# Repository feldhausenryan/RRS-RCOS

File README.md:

# RRS-RCOS
Open Source Schematics, Code, etc.

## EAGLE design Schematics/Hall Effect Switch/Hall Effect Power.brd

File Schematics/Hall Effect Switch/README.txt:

The hall effect switch is a magnetic on/off switch.

Applying a magnet will turn the switch ON or OFF, causing the input Vin+ and Gnd to be applied to Vout+ and Gnd.
Reversing the magnetic field will reverse the state of the switch.

STATUS: 
Hall Effect Power.brd - Broken

TODO: Add parts list

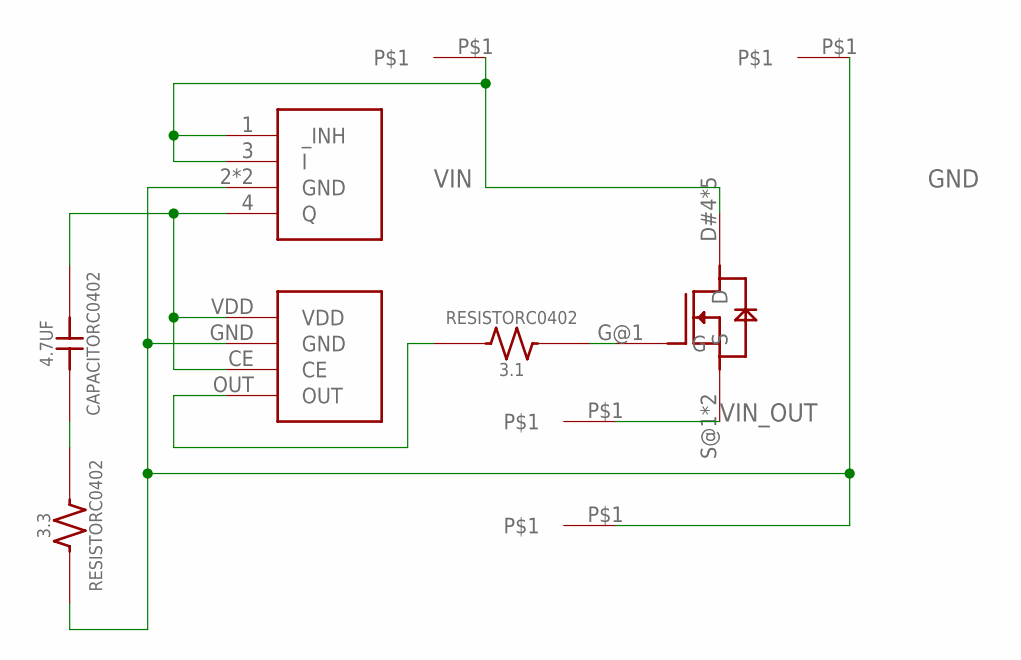
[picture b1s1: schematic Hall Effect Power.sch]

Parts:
3.1: RESISTORC0402; C0402; DIGIKEY# 1276-4368-1-ND
3.3: RESISTORC0402; C0402; DIGIKEY# 311-3.3JRCT-ND
4.7UF: CAPACITORC0402; C0402; DIGIKEY# 1276-6819-1-ND
U$1: HALL-MOSFET-NEW; DIGIKEY# SIAA40DJ-T1-GE3CT-ND
U$2: HALL-HALL-NEW; DIGIKEY# 1662-1657-1-ND
U$3: HALL-REG-NEW; DIGIKEY# IFX20001MBV33HTSA1CT-ND
U$4, U$5, U$6, U$7: SINGLE-WIRE

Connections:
GND: 3.3.1, U$2.GND, U$3.2 (GND), U$3.5 (GND), U$4.P$1, U$7.P$1
HALL_OUT: 3.1.2, U$2.OUT
unnamed: 4.7UF.2 (B), U$2.CE, U$2.VDD, U$3.4 (Q)
unnamed: 3.3.2, 4.7UF.1 (A)
unnamed: 3.1.1, U$1.G@1 (G)
VIN: U$1.D#4 (D), U$1.D@1 (D), U$1.D@2 (D), U$1.D@3 (D), U$1.D@5 (D), U$3.1 (_INH), U$3.3 (I), U$6.P$1
VIN_OUT: U$1.S@1 (S), U$1.S@2 (S), U$5.P$1

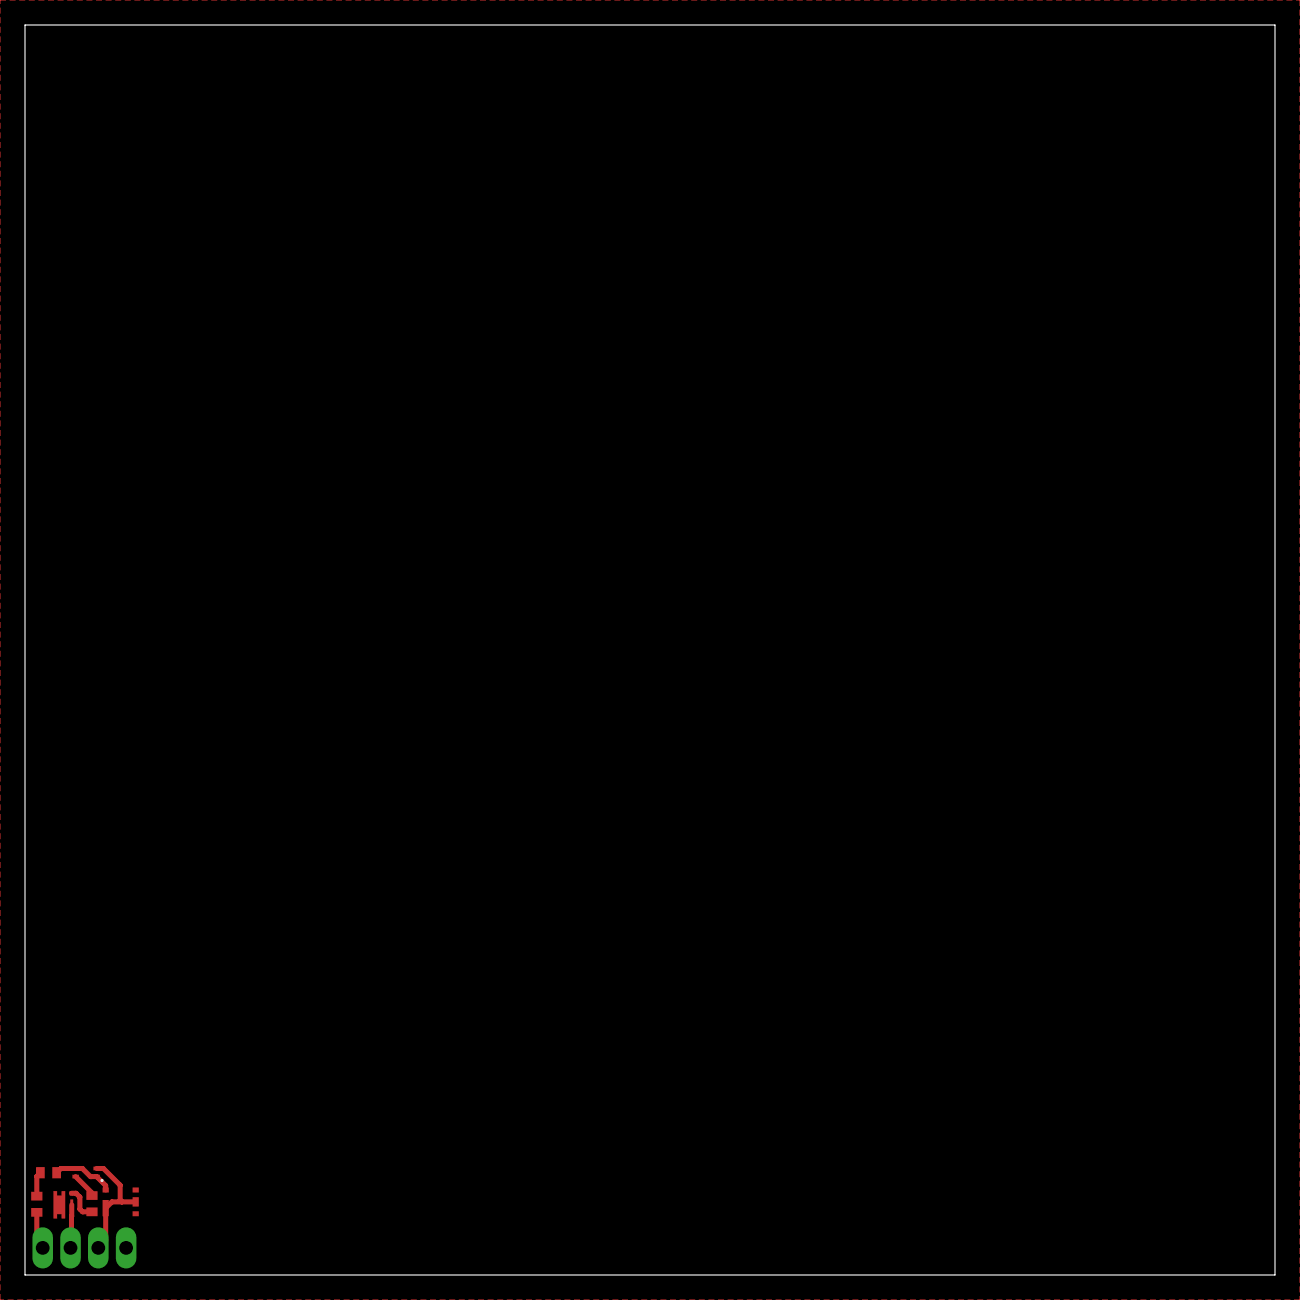
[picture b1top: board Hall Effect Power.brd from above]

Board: 2 copper layers, 100.0 x 100.0 mm, 10 parts (0 on the bottom side), 7 nets.

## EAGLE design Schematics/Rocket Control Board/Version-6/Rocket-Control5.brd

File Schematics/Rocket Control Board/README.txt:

October 18, 2016 by Ryan Feldhausen

The Rocket Control Board is an Arduino Zero clone. 
In the future the board will be used to mount various surface mounted components to 
create an Arduino compatible rocket control board.

Folder Contents
Misc - Various pictures or other files that may aid the development or understanding
       of the schematics or boards in this section.
	   
Version - The various stages of development of the schematic / board for this section. 
          There is no guarantee that any of the Version-X folders will contain 
		  functional schematics or boards.

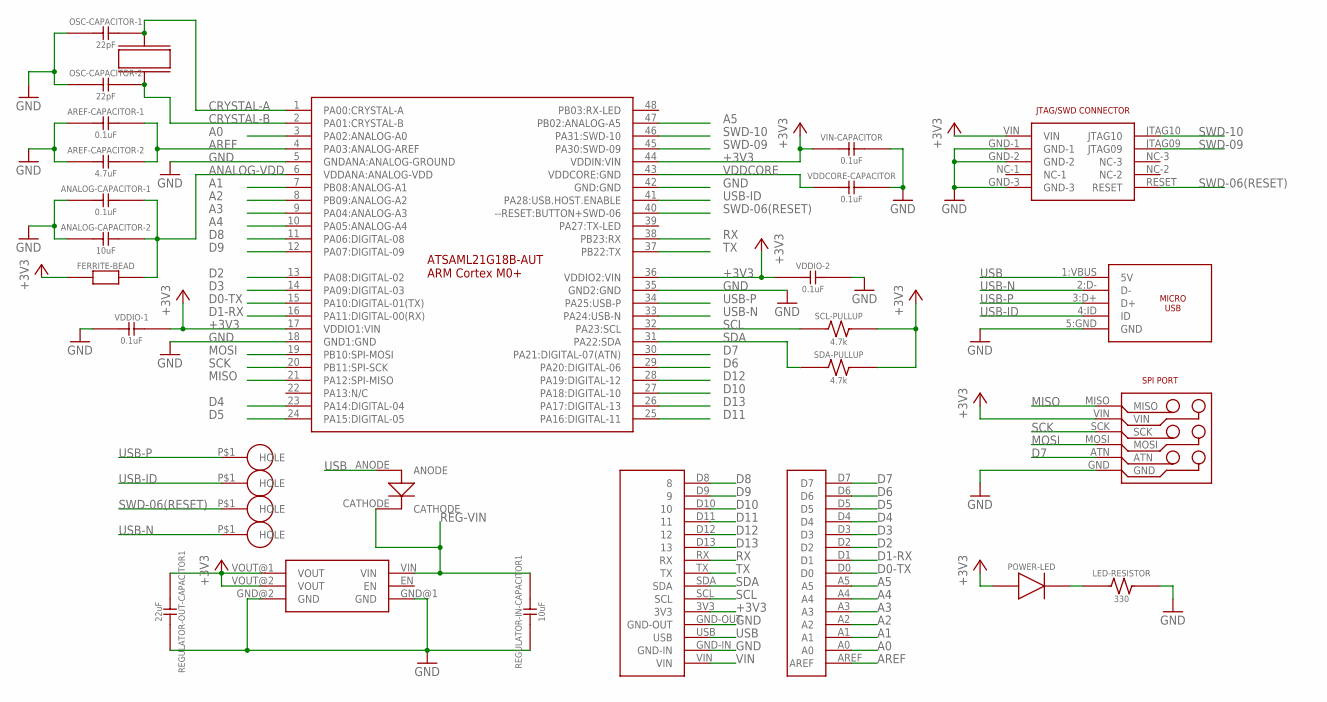
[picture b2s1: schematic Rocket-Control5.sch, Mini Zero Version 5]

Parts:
ANALOG-CAPACITOR-1: 0.1uF; C0402; DIGIKEY# 1276-1022-1-ND
ANALOG-CAPACITOR-2: 10uF; C0402; DIGIKEY# 1276-1450-1-ND
AREF-CAPACITOR-1: 0.1uF; C0402; DIGIKEY# 1276-1022-1-ND
AREF-CAPACITOR-2: 4.7uF; C0402; DIGIKEY# 1276-1173-1-ND
ARM-CORTEX-MO+: ATSAML21G18B-AUT; TQFP48; DIGIKEY# 1611-ATSAML21G18B-AUTCT-ND
FERRITE-BEAD: BLM18PG471SN1D; C0603; DIGIKEY# 490-5223-1-ND
HEADER-SIDE-A: HEADER-SIDE-A
HEADER-SIDE-B: HEADER-SIDE-B; DIGIKEY# S1011EC-40-ND
JTAG-CONNECTOR: JTAG-MINI; DIGIKEY# 609-3712-ND
LED-RESISTOR: 330; C0603; DIGIKEY# 1276-5050-1-ND
MICRO-USB-CONNECTOR: 10118194-0001LF; DIGIKEY# 609-4618-1-ND
OSC-CAPACITOR-1, OSC-CAPACITOR-2: 22pF; C0603; DIGIKEY# 1276-2229-1-ND
POWER-LED: APTD1608ZGC; C0603; DIGIKEY# 754-1547-1-ND
REGULATOR-IN-CAPACITOR1: 10uF; C0402; DIGIKEY# 1276-1450-1-ND
REGULATOR-OUT-CAPACITOR1: 22uF; C0402; DIGIKEY# 1276-6834-1-ND
SCL-PULLUP: 4.7k; C0402; DIGIKEY# 1276-5078-1-ND
SDA-PULLUP: 4.7k; C0402; DIGIKEY# 1276-5078-1-ND
SPI-PORT: SPI-PORT
U$1: ABS07-32.768KHZ-T
U$2: MIC5528
U$3: DIODE-STANDARD
U$4, U$5, U$6, U$7: HEADER-HOLE
VDDCORE-CAPACITOR: 0.1uF; C0402; DIGIKEY# 1276-1022-1-ND
VDDIO-1, VDDIO-2: 0.1uF; C0402; DIGIKEY# 1276-1022-1-ND
VIN-CAPACITOR: 0.1uF; C0402; DIGIKEY# 1276-1022-1-ND

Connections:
+3V3: ARM-CORTEX-MO+.17 (VDDIO1:VIN), ARM-CORTEX-MO+.36 (VDDIO2:VIN), ARM-CORTEX-MO+.44 (VDDIN:VIN), FERRITE-BEAD.1, HEADER-SIDE-B.3V3, JTAG-CONNECTOR.VIN, POWER-LED.1, REGULATOR-OUT-CAPACITOR1.1 (A), SCL-PULLUP.2, SDA-PULLUP.2, SPI-PORT.VIN, U$2.VOUT@1 (VOUT), U$2.VOUT@2 (VOUT), VDDIO-1.2 (B), VDDIO-2.2 (B), VIN-CAPACITOR.1 (A)
A0: ARM-CORTEX-MO+.3 (PA02:ANALOG-A0), HEADER-SIDE-A.A0
A1: ARM-CORTEX-MO+.7 (PB08:ANALOG-A1), HEADER-SIDE-A.A1
A2: ARM-CORTEX-MO+.8 (PB09:ANALOG-A2), HEADER-SIDE-A.A2
A3: ARM-CORTEX-MO+.9 (PA04:ANALOG-A3), HEADER-SIDE-A.A3
A4: ARM-CORTEX-MO+.10 (PA05:ANALOG-A4), HEADER-SIDE-A.A4
A5: ARM-CORTEX-MO+.47 (PB02:ANALOG-A5), HEADER-SIDE-A.A5
ANALOG-VDD: ANALOG-CAPACITOR-1.2 (B), ANALOG-CAPACITOR-2.2 (B), ARM-CORTEX-MO+.6 (VDDANA:ANALOG-VDD), FERRITE-BEAD.2
AREF: AREF-CAPACITOR-1.2 (B), AREF-CAPACITOR-2.2 (B), ARM-CORTEX-MO+.4 (PA03:ANALOG-AREF), HEADER-SIDE-A.AREF
CRYSTAL-A: ARM-CORTEX-MO+.1 (PA00:CRYSTAL-A), OSC-CAPACITOR-1.2 (B), U$1.P$2
CRYSTAL-B: ARM-CORTEX-MO+.2 (PA01:CRYSTAL-B), OSC-CAPACITOR-2.2 (B), U$1.P$1
D0-TX: ARM-CORTEX-MO+.15 (PA10:DIGITAL-01(TX)), HEADER-SIDE-A.D0
D1-RX: ARM-CORTEX-MO+.16 (PA11:DIGITAL-00(RX)), HEADER-SIDE-A.D1
D2: ARM-CORTEX-MO+.13 (PA08:DIGITAL-02), HEADER-SIDE-A.D2
D3: ARM-CORTEX-MO+.14 (PA09:DIGITAL-03), HEADER-SIDE-A.D3
D4: ARM-CORTEX-MO+.23 (PA14:DIGITAL-04), HEADER-SIDE-A.D4
D5: ARM-CORTEX-MO+.24 (PA15:DIGITAL-05), HEADER-SIDE-A.D5
D6: ARM-CORTEX-MO+.29 (PA20:DIGITAL-06), HEADER-SIDE-A.D6
D7: ARM-CORTEX-MO+.30 (PA21:DIGITAL-07(ATN)), HEADER-SIDE-A.D7, SPI-PORT.ATN
D8: ARM-CORTEX-MO+.11 (PA06:DIGITAL-08), HEADER-SIDE-B.D8 (8)
D9: ARM-CORTEX-MO+.12 (PA07:DIGITAL-09), HEADER-SIDE-B.D9 (9)
D10: ARM-CORTEX-MO+.27 (PA18:DIGITAL-10), HEADER-SIDE-B.D10 (10)
D11: ARM-CORTEX-MO+.25 (PA16:DIGITAL-11), HEADER-SIDE-B.D11 (11)
D12: ARM-CORTEX-MO+.28 (PA19:DIGITAL-12), HEADER-SIDE-B.D12 (12)
D13: ARM-CORTEX-MO+.26 (PA17:DIGITAL-13), HEADER-SIDE-B.D13 (13)
GND: ANALOG-CAPACITOR-1.1 (A), ANALOG-CAPACITOR-2.1 (A), AREF-CAPACITOR-1.1 (A), AREF-CAPACITOR-2.1 (A), ARM-CORTEX-MO+.5 (GNDANA:ANALOG-GROUND), ARM-CORTEX-MO+.18 (GND1:GND), ARM-CORTEX-MO+.35 (GND2:GND), ARM-CORTEX-MO+.42 (GND:GND), HEADER-SIDE-B.GND-IN, HEADER-SIDE-B.GND-OUT, JTAG-CONNECTOR.GND-1, JTAG-CONNECTOR.GND-2, JTAG-CONNECTOR.GND-3, LED-RESISTOR.2, MICRO-USB-CONNECTOR.5:GND (GND), OSC-CAPACITOR-1.1 (A), OSC-CAPACITOR-2.1 (A), REGULATOR-IN-CAPACITOR1.1 (A), REGULATOR-OUT-CAPACITOR1.2 (B), SPI-PORT.GND, U$2.GND@1 (GND), U$2.GND@2 (GND), VDDCORE-CAPACITOR.2 (B), VDDIO-1.1 (A), VDDIO-2.1 (A), VIN-CAPACITOR.2 (B)
MISO: ARM-CORTEX-MO+.21 (PA12:SPI-MISO), SPI-PORT.MISO
MOSI: ARM-CORTEX-MO+.19 (PB10:SPI-MOSI), SPI-PORT.MOSI
unnamed: LED-RESISTOR.1, POWER-LED.2
REG-VIN: REGULATOR-IN-CAPACITOR1.2 (B), U$2.VIN, U$3.CATHODE
RX: ARM-CORTEX-MO+.38 (PB23:RX), HEADER-SIDE-B.RX
SCK: ARM-CORTEX-MO+.20 (PB11:SPI-SCK), SPI-PORT.SCK
SCL: ARM-CORTEX-MO+.32 (PA23:SCL), HEADER-SIDE-B.SCL, SCL-PULLUP.1
SDA: ARM-CORTEX-MO+.31 (PA22:SDA), HEADER-SIDE-B.SDA, SDA-PULLUP.1
SWD-06(RESET): ARM-CORTEX-MO+.40 (--RESET:BUTTON+SWD-06), JTAG-CONNECTOR.RESET, U$5.P$1
SWD-09: ARM-CORTEX-MO+.45 (PA30:SWD-09), JTAG-CONNECTOR.JTAG09
SWD-10: ARM-CORTEX-MO+.46 (PA31:SWD-10), JTAG-CONNECTOR.JTAG10
TX: ARM-CORTEX-MO+.37 (PB22:TX), HEADER-SIDE-B.TX
USB: HEADER-SIDE-B.USB, MICRO-USB-CONNECTOR.1:VBUS (5V), U$3.ANODE
USB-ID: ARM-CORTEX-MO+.41 (PA28:USB.HOST.ENABLE), MICRO-USB-CONNECTOR.4:ID (ID), U$4.P$1
USB-N: ARM-CORTEX-MO+.33 (PA24:USB-N), MICRO-USB-CONNECTOR.2:D- (D-), U$6.P$1
USB-P: ARM-CORTEX-MO+.34 (PA25:USB-P), MICRO-USB-CONNECTOR.3:D+ (D+), U$7.P$1
VDDCORE: ARM-CORTEX-MO+.43 (VDDCORE:GND), VDDCORE-CAPACITOR.1 (A)
VIN: HEADER-SIDE-B.VIN

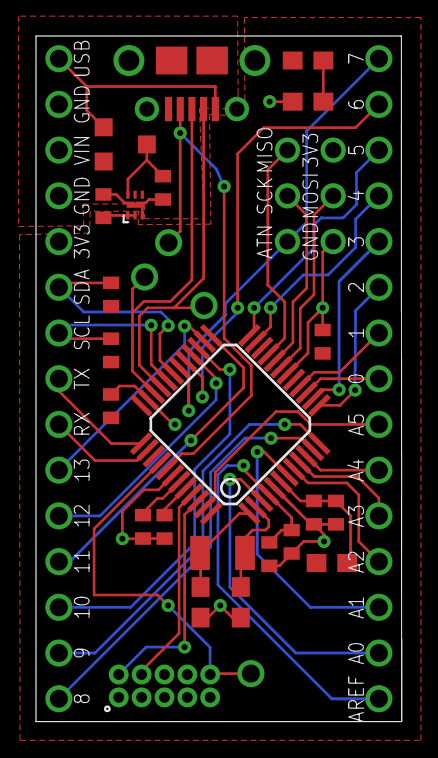
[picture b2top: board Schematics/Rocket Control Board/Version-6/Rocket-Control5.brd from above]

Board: 2 copper layers, 20.3 x 38.1 mm, 30 parts (0 on the bottom side), 43 nets.

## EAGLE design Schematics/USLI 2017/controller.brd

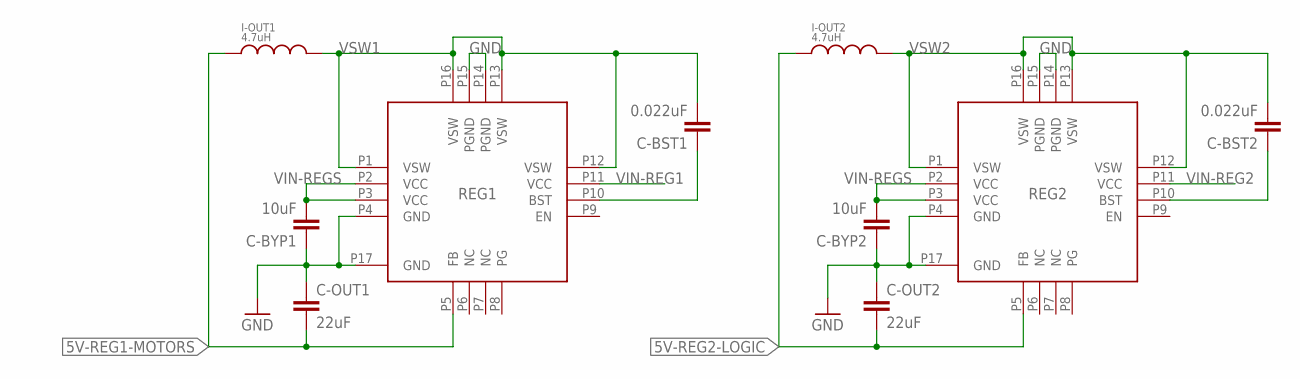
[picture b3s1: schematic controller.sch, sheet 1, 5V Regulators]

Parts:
C-BST1, C-BST2: 0.022uF; C1608; DIGIKEY# 1276-1104-1-ND
C-BYP1, C-BYP2: 10uF; C3216; DIGIKEY# 490-5524-1-ND
C-OUT1, C-OUT2: 22uF; C2012; DIGIKEY# 445-7664-1-ND
I-OUT1, I-OUT2: 4.7uH; ASPI-0628-4R7M-T1
REG1, REG2: TS30012-M050QFNR

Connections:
5V-REG1-MOTORS: C-OUT1.2, I-OUT1.P$1, REG1.P5 (FB); also elsewhere on the board
5V-REG2-LOGIC: C-OUT2.2, I-OUT2.P$1, REG2.P5 (FB); also elsewhere on the board
GND: C-BYP1.1, C-BYP2.1, C-OUT1.1, C-OUT2.1, REG1.P4 (GND), REG1.P14 (PGND), REG1.P15 (PGND), REG1.P17 (GND), REG2.P4 (GND), REG2.P14 (PGND), REG2.P15 (PGND), REG2.P17 (GND); also elsewhere on the board
unnamed: C-BST1.1, REG1.P10 (BST)
unnamed: C-BST2.1, REG2.P10 (BST)
VIN-REG1: REG1.P11 (VCC)
VIN-REG2: REG2.P11 (VCC)
VIN-REGS: C-BYP1.2, C-BYP2.2, REG1.P2 (VCC), REG1.P3 (VCC), REG2.P2 (VCC), REG2.P3 (VCC); also elsewhere on the board
VSW1: C-BST1.2, I-OUT1.P$2, REG1.P1 (VSW), REG1.P12 (VSW), REG1.P13 (VSW), REG1.P16 (VSW)
VSW2: C-BST2.2, I-OUT2.P$2, REG2.P1 (VSW), REG2.P12 (VSW), REG2.P13 (VSW), REG2.P16 (VSW)

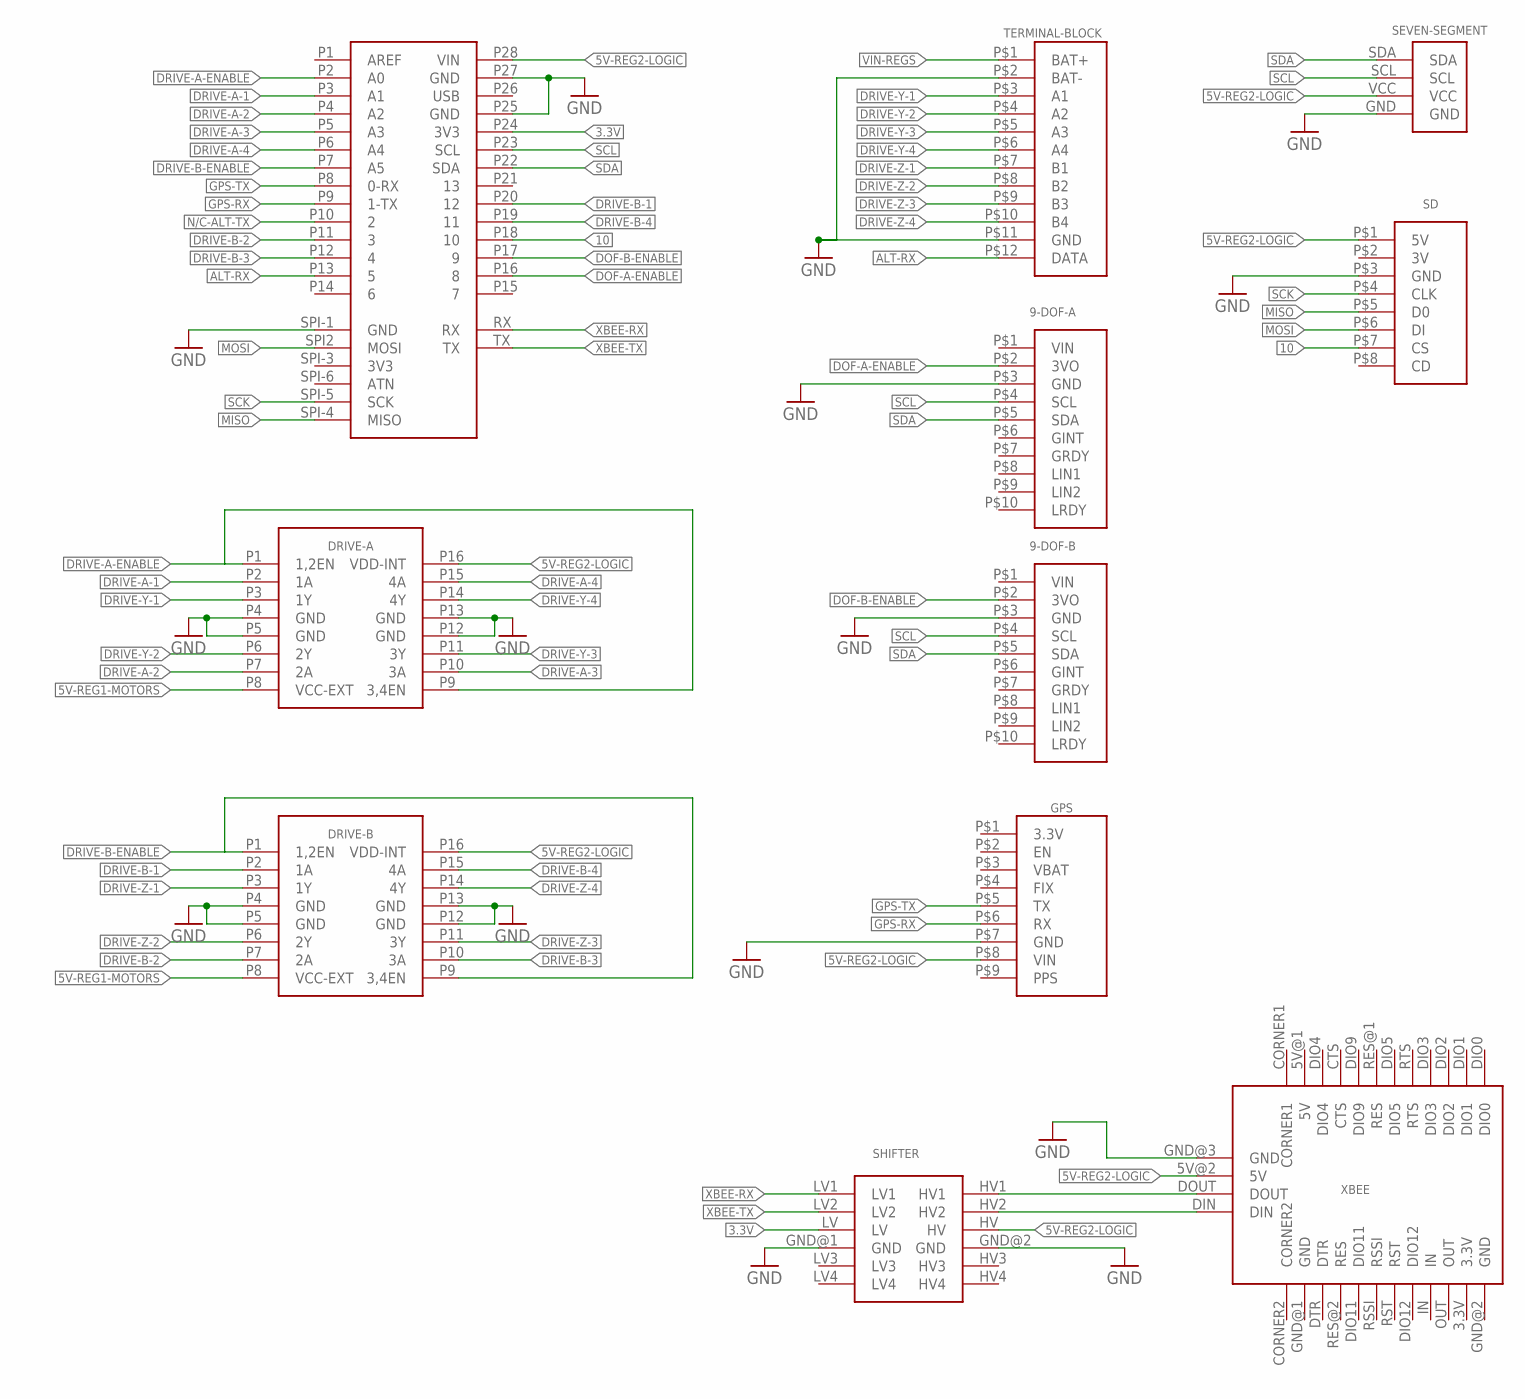
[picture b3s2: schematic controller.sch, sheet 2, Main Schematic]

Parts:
9-DOF-A, 9-DOF-B: ADAFRUIT-9-DOF
DRIVE-A: SN754410
DRIVE-B: SN754410
GPS: ADAFRUIT-GPS-BREAKOUT
NEUTRINO: NEUTRINO
SD: ADAFRUIT-MICRO-SD
SEVEN-SEGMENT: ADAFRUIT-7-SEGMENT
SHIFTER: SPARKFUN-LEVEL-SHIFTER
TERMINAL-BLOCK: 1725753
XBEE: XBEE-BREAKOUT

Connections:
3.3V: NEUTRINO.P24 (3V3), SHIFTER.LV
5V-REG1-MOTORS: DRIVE-A.P8 (VCC-EXT), DRIVE-B.P8 (VCC-EXT); also elsewhere on the board
5V-REG2-LOGIC: DRIVE-A.P16 (VDD-INT), DRIVE-B.P16 (VDD-INT), GPS.P$8 (VIN), NEUTRINO.P28 (VIN), SD.P$1 (5V), SEVEN-SEGMENT.VCC, SHIFTER.HV, XBEE.5V@2 (5V); also elsewhere on the board
10: NEUTRINO.P18 (10), SD.P$7 (CS)
ALT-RX: NEUTRINO.P13 (5), TERMINAL-BLOCK.P$12 (DATA)
DOF-A-ENABLE: 9-DOF-A.P$2 (3VO), NEUTRINO.P16 (8)
DOF-B-ENABLE: 9-DOF-B.P$2 (3VO), NEUTRINO.P17 (9)
DRIVE-A-1: DRIVE-A.P2 (1A), NEUTRINO.P3 (A1)
DRIVE-A-2: DRIVE-A.P7 (2A), NEUTRINO.P4 (A2)
DRIVE-A-3: DRIVE-A.P10 (3A), NEUTRINO.P5 (A3)
DRIVE-A-4: DRIVE-A.P15 (4A), NEUTRINO.P6 (A4)
DRIVE-A-ENABLE: DRIVE-A.P1 (1,2EN), DRIVE-A.P9 (3,4EN), NEUTRINO.P2 (A0)
DRIVE-B-1: DRIVE-B.P2 (1A), NEUTRINO.P20 (12)
DRIVE-B-2: DRIVE-B.P7 (2A), NEUTRINO.P11 (3)
DRIVE-B-3: DRIVE-B.P10 (3A), NEUTRINO.P12 (4)
DRIVE-B-4: DRIVE-B.P15 (4A), NEUTRINO.P19 (11)
DRIVE-B-ENABLE: DRIVE-B.P1 (1,2EN), DRIVE-B.P9 (3,4EN), NEUTRINO.P7 (A5)
DRIVE-Y-1: DRIVE-A.P3 (1Y), TERMINAL-BLOCK.P$3 (A1)
DRIVE-Y-2: DRIVE-A.P6 (2Y), TERMINAL-BLOCK.P$4 (A2)
DRIVE-Y-3: DRIVE-A.P11 (3Y), TERMINAL-BLOCK.P$5 (A3)
DRIVE-Y-4: DRIVE-A.P14 (4Y), TERMINAL-BLOCK.P$6 (A4)
DRIVE-Z-1: DRIVE-B.P3 (1Y), TERMINAL-BLOCK.P$7 (B1)
DRIVE-Z-2: DRIVE-B.P6 (2Y), TERMINAL-BLOCK.P$8 (B2)
DRIVE-Z-3: DRIVE-B.P11 (3Y), TERMINAL-BLOCK.P$9 (B3)
DRIVE-Z-4: DRIVE-B.P14 (4Y), TERMINAL-BLOCK.P$10 (B4)
GND: 9-DOF-A.P$3 (GND), 9-DOF-B.P$3 (GND), DRIVE-A.P4 (GND), DRIVE-A.P5 (GND), DRIVE-A.P12 (GND), DRIVE-A.P13 (GND), DRIVE-B.P4 (GND), DRIVE-B.P5 (GND), DRIVE-B.P12 (GND), DRIVE-B.P13 (GND), GPS.P$7 (GND), NEUTRINO.P25 (GND), NEUTRINO.P27 (GND), NEUTRINO.SPI-1 (GND), SD.P$3 (GND), SEVEN-SEGMENT.GND, SHIFTER.GND@1 (GND), SHIFTER.GND@2 (GND), TERMINAL-BLOCK.P$2 (BAT-), TERMINAL-BLOCK.P$11 (GND), XBEE.GND@3 (GND); also elsewhere on the board
GPS-RX: GPS.P$6 (RX), NEUTRINO.P9 (1-TX)
GPS-TX: GPS.P$5 (TX), NEUTRINO.P8 (0-RX)
HV1: SHIFTER.HV1, XBEE.DOUT
HV2: SHIFTER.HV2, XBEE.DIN
MISO: NEUTRINO.SPI-4 (MISO), SD.P$5 (D0)
MOSI: NEUTRINO.SPI2 (MOSI), SD.P$6 (DI)
N/C-ALT-TX: NEUTRINO.P10 (2)
SCK: NEUTRINO.SPI-5 (SCK), SD.P$4 (CLK)
SCL: 9-DOF-A.P$4 (SCL), 9-DOF-B.P$4 (SCL), NEUTRINO.P23 (SCL), SEVEN-SEGMENT.SCL
SDA: 9-DOF-A.P$5 (SDA), 9-DOF-B.P$5 (SDA), NEUTRINO.P22 (SDA), SEVEN-SEGMENT.SDA
VIN-REGS: TERMINAL-BLOCK.P$1 (BAT+); also elsewhere on the board
XBEE-RX: NEUTRINO.RX, SHIFTER.LV1
XBEE-TX: NEUTRINO.TX, SHIFTER.LV2

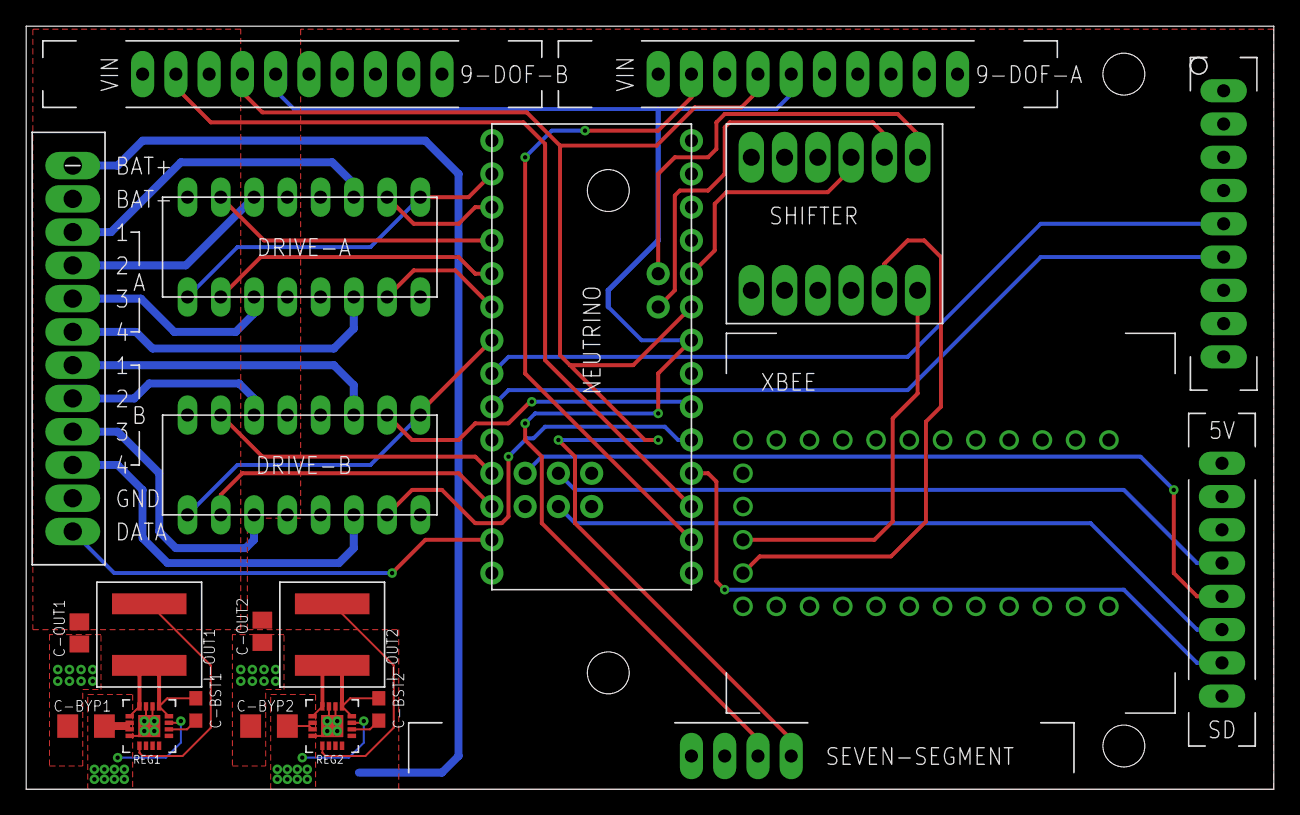
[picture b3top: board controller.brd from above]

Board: 2 copper layers, 95.3 x 58.3 mm, 21 parts (0 on the bottom side), 42 nets.

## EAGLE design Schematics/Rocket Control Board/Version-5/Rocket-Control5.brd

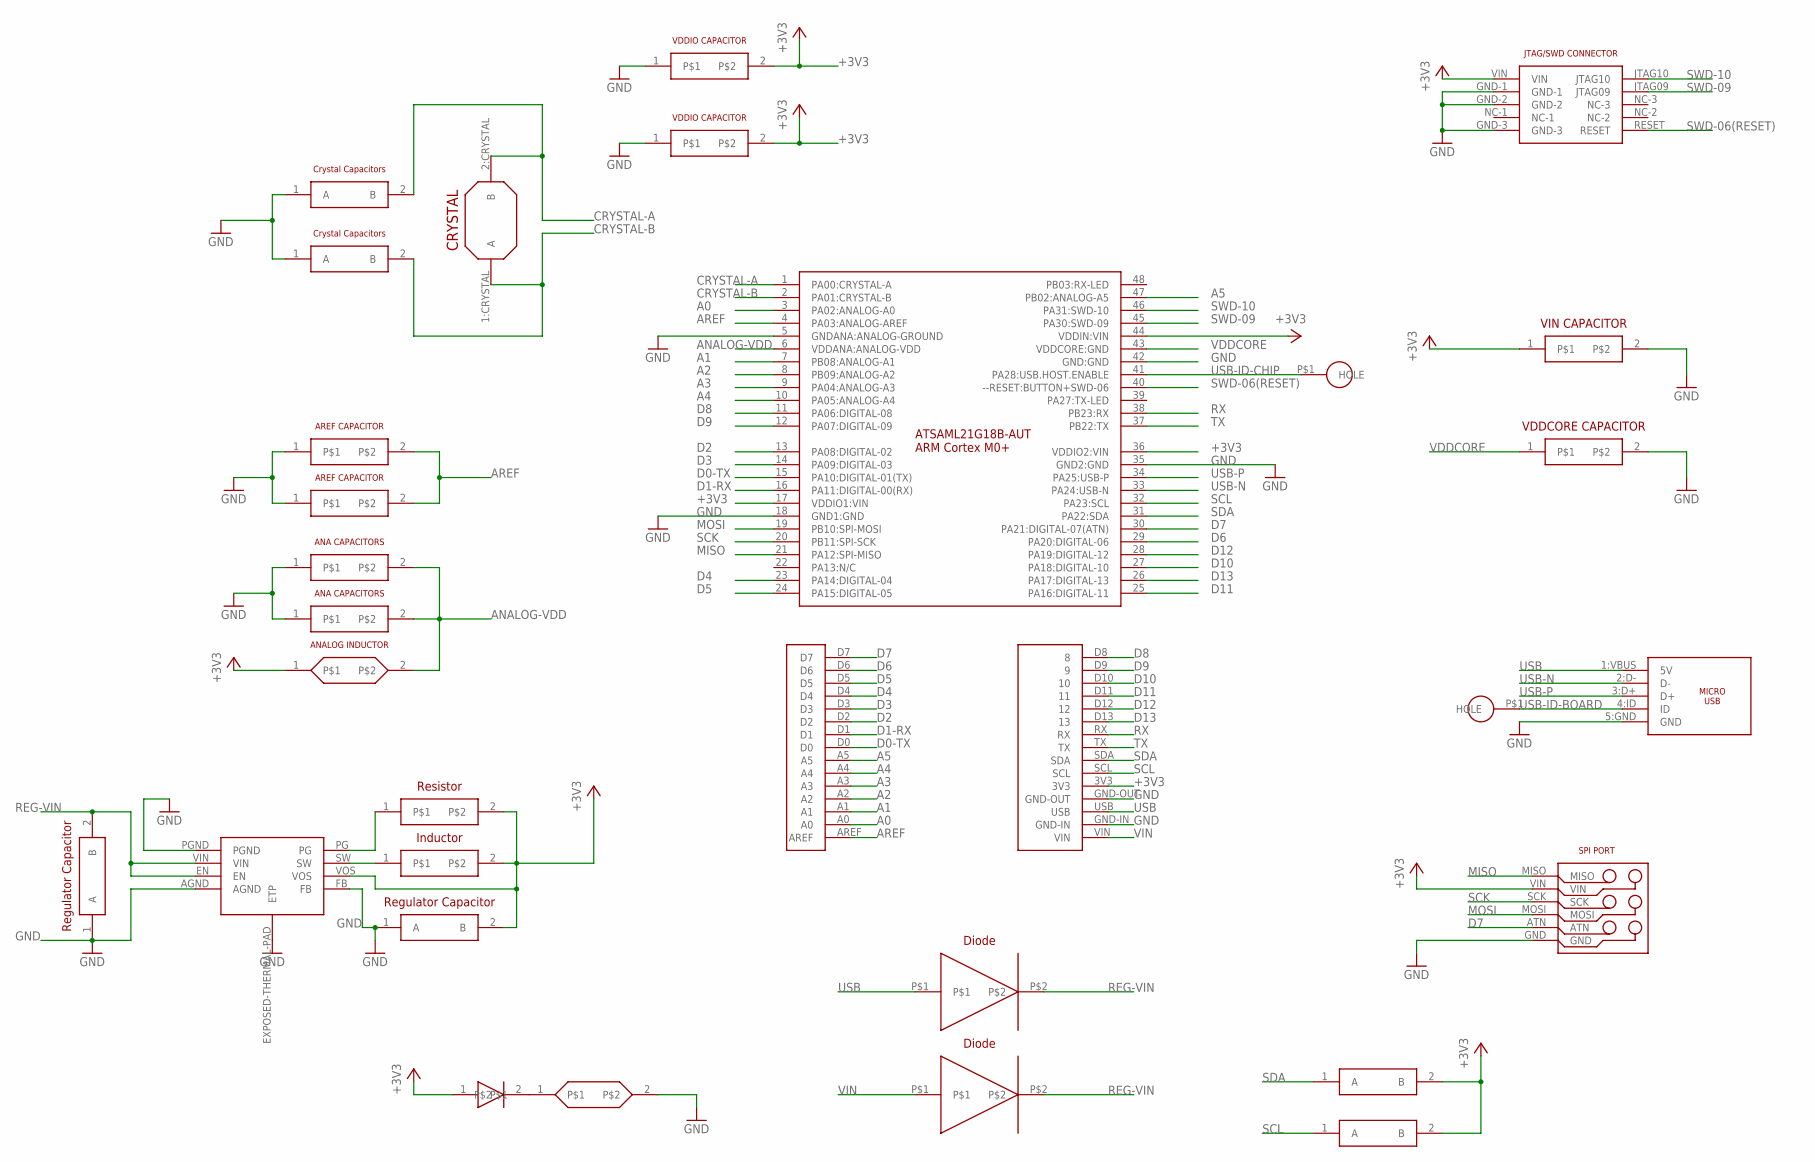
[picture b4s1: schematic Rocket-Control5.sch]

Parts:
U$1: ATSAML21G18B-AUT; TQFP48
U$2, U$3: CRYSTAL-CAPACITORS; C0603
U$4: CRYSTAL; 4-SOJ:CRYSTAL
U$5: REGULATOR; 8-WFDFN-EXPOSED-PAD
U$6, U$7: AREF-CAPACITORS; C0402
U$8, U$9: ANALOG-CAPACITORS; C0402
U$10: ANALOG-INDUCTOR; C0603
U$11, U$12: REGULATOR-CAPACITORS; C0402
U$13: REGULATOR-INDUCTOR; C0603
U$14: REGULATOR-RESISTOR; C0603
U$15, U$16: REGULATION-DIODE; SOD-882
U$17: LED; C0603
U$18: LED-RESISTOR; C0603
U$19, U$20: I2C-PULLUP; C0402
U$21: HEADER-SIDE-A
U$22: HEADER-SIDE-B
U$23, U$24: HEADER-HOLE
U$26, U$35: VDDIO-CAPACITOR; C0402
U$38: 10118194-0001LF:MICRO-USB; 10118194-0001LF:MICRO-USB-B
U$41: SPI-PORT
U$56: VDDCORE-CAPACITOR; C0402
U$57: VIN-CAPACITOR; C0402
U$61: JTAG-MINI

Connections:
+3V3: U$1.17 (VDDIO1:VIN), U$1.36 (VDDIO2:VIN), U$1.44 (VDDIN:VIN), U$5.VOS, U$10.1, U$12.2 (B), U$13.2, U$14.2, U$17.1, U$19.2 (B), U$20.2 (B), U$22.3V3, U$26.2, U$35.2, U$41.VIN, U$57.1, U$61.VIN
A0: U$1.3 (PA02:ANALOG-A0), U$21.A0
A1: U$1.7 (PB08:ANALOG-A1), U$21.A1
A2: U$1.8 (PB09:ANALOG-A2), U$21.A2
A3: U$1.9 (PA04:ANALOG-A3), U$21.A3
A4: U$1.10 (PA05:ANALOG-A4), U$21.A4
A5: U$1.47 (PB02:ANALOG-A5), U$21.A5
ANALOG-VDD: U$1.6 (VDDANA:ANALOG-VDD), U$8.2, U$9.2, U$10.2
AREF: U$1.4 (PA03:ANALOG-AREF), U$6.2, U$7.2, U$21.AREF
CRYSTAL-A: U$1.1 (PA00:CRYSTAL-A), U$2.2 (B), U$4.2:CRYSTAL (B)
CRYSTAL-B: U$1.2 (PA01:CRYSTAL-B), U$3.2 (B), U$4.1:CRYSTAL (A)
D0-TX: U$1.15 (PA10:DIGITAL-01(TX)), U$21.D0
D1-RX: U$1.16 (PA11:DIGITAL-00(RX)), U$21.D1
D2: U$1.13 (PA08:DIGITAL-02), U$21.D2
D3: U$1.14 (PA09:DIGITAL-03), U$21.D3
D4: U$1.23 (PA14:DIGITAL-04), U$21.D4
D5: U$1.24 (PA15:DIGITAL-05), U$21.D5
D6: U$1.29 (PA20:DIGITAL-06), U$21.D6
D7: U$1.30 (PA21:DIGITAL-07(ATN)), U$21.D7, U$41.ATN
D8: U$1.11 (PA06:DIGITAL-08), U$22.D8 (8)
D9: U$1.12 (PA07:DIGITAL-09), U$22.D9 (9)
D10: U$1.27 (PA18:DIGITAL-10), U$22.D10 (10)
D11: U$1.25 (PA16:DIGITAL-11), U$22.D11 (11)
D12: U$1.28 (PA19:DIGITAL-12), U$22.D12 (12)
D13: U$1.26 (PA17:DIGITAL-13), U$22.D13 (13)
GND: U$1.5 (GNDANA:ANALOG-GROUND), U$1.18 (GND1:GND), U$1.35 (GND2:GND), U$1.42 (GND:GND), U$2.1 (A), U$3.1 (A), U$5.AGND, U$5.EXPOSED-THERMAL-PAD (ETP), U$5.FB, U$5.PGND, U$6.1, U$7.1, U$8.1, U$9.1, U$11.1 (A), U$12.1 (A), U$18.2, U$22.GND-IN, U$22.GND-OUT, U$26.1, U$35.1, U$38.5:GND (GND), U$41.GND, U$56.2, U$57.2, U$61.GND-1, U$61.GND-2, U$61.GND-3
MISO: U$1.21 (PA12:SPI-MISO), U$41.MISO
MOSI: U$1.19 (PB10:SPI-MOSI), U$41.MOSI
unnamed: U$5.SW, U$13.1
unnamed: U$17.2, U$18.1
unnamed: U$5.PG, U$14.1
REG-VIN: U$5.EN, U$5.VIN, U$11.2 (B), U$15.P$2, U$16.P$2
RX: U$1.38 (PB23:RX), U$22.RX
SCK: U$1.20 (PB11:SPI-SCK), U$41.SCK
SCL: U$1.32 (PA23:SCL), U$20.1 (A), U$22.SCL
SDA: U$1.31 (PA22:SDA), U$19.1 (A), U$22.SDA
SWD-06(RESET): U$1.40 (--RESET:BUTTON+SWD-06), U$61.RESET
SWD-09: U$1.45 (PA30:SWD-09), U$61.JTAG09
SWD-10: U$1.46 (PA31:SWD-10), U$61.JTAG10
TX: U$1.37 (PB22:TX), U$22.TX
USB: U$15.P$1, U$22.USB, U$38.1:VBUS (5V)
USB-ID-BOARD: U$23.P$1, U$38.4:ID (ID)
USB-ID-CHIP: U$1.41 (PA28:USB.HOST.ENABLE), U$24.P$1
USB-N: U$1.33 (PA24:USB-N), U$38.2:D- (D-)
USB-P: U$1.34 (PA25:USB-P), U$38.3:D+ (D+)
VDDCORE: U$1.43 (VDDCORE:GND), U$56.1
VIN: U$16.P$1, U$22.VIN

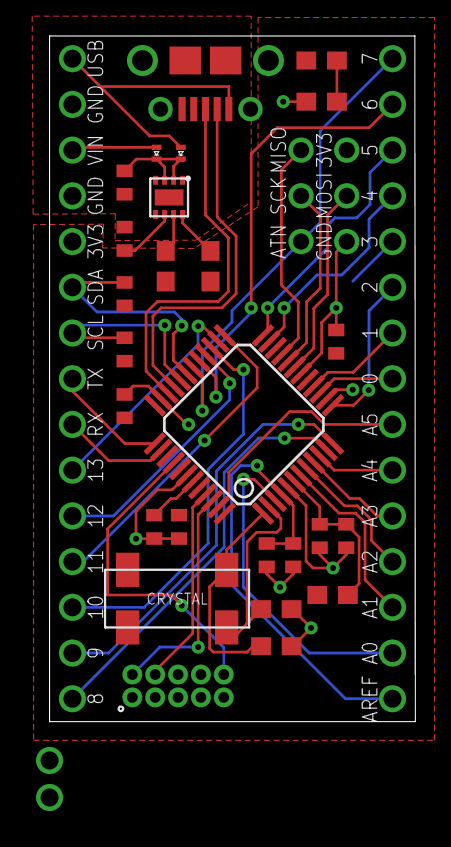
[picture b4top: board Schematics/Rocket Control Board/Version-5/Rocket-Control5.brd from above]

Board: 2 copper layers, 20.3 x 38.1 mm, 31 parts (0 on the bottom side), 47 nets.

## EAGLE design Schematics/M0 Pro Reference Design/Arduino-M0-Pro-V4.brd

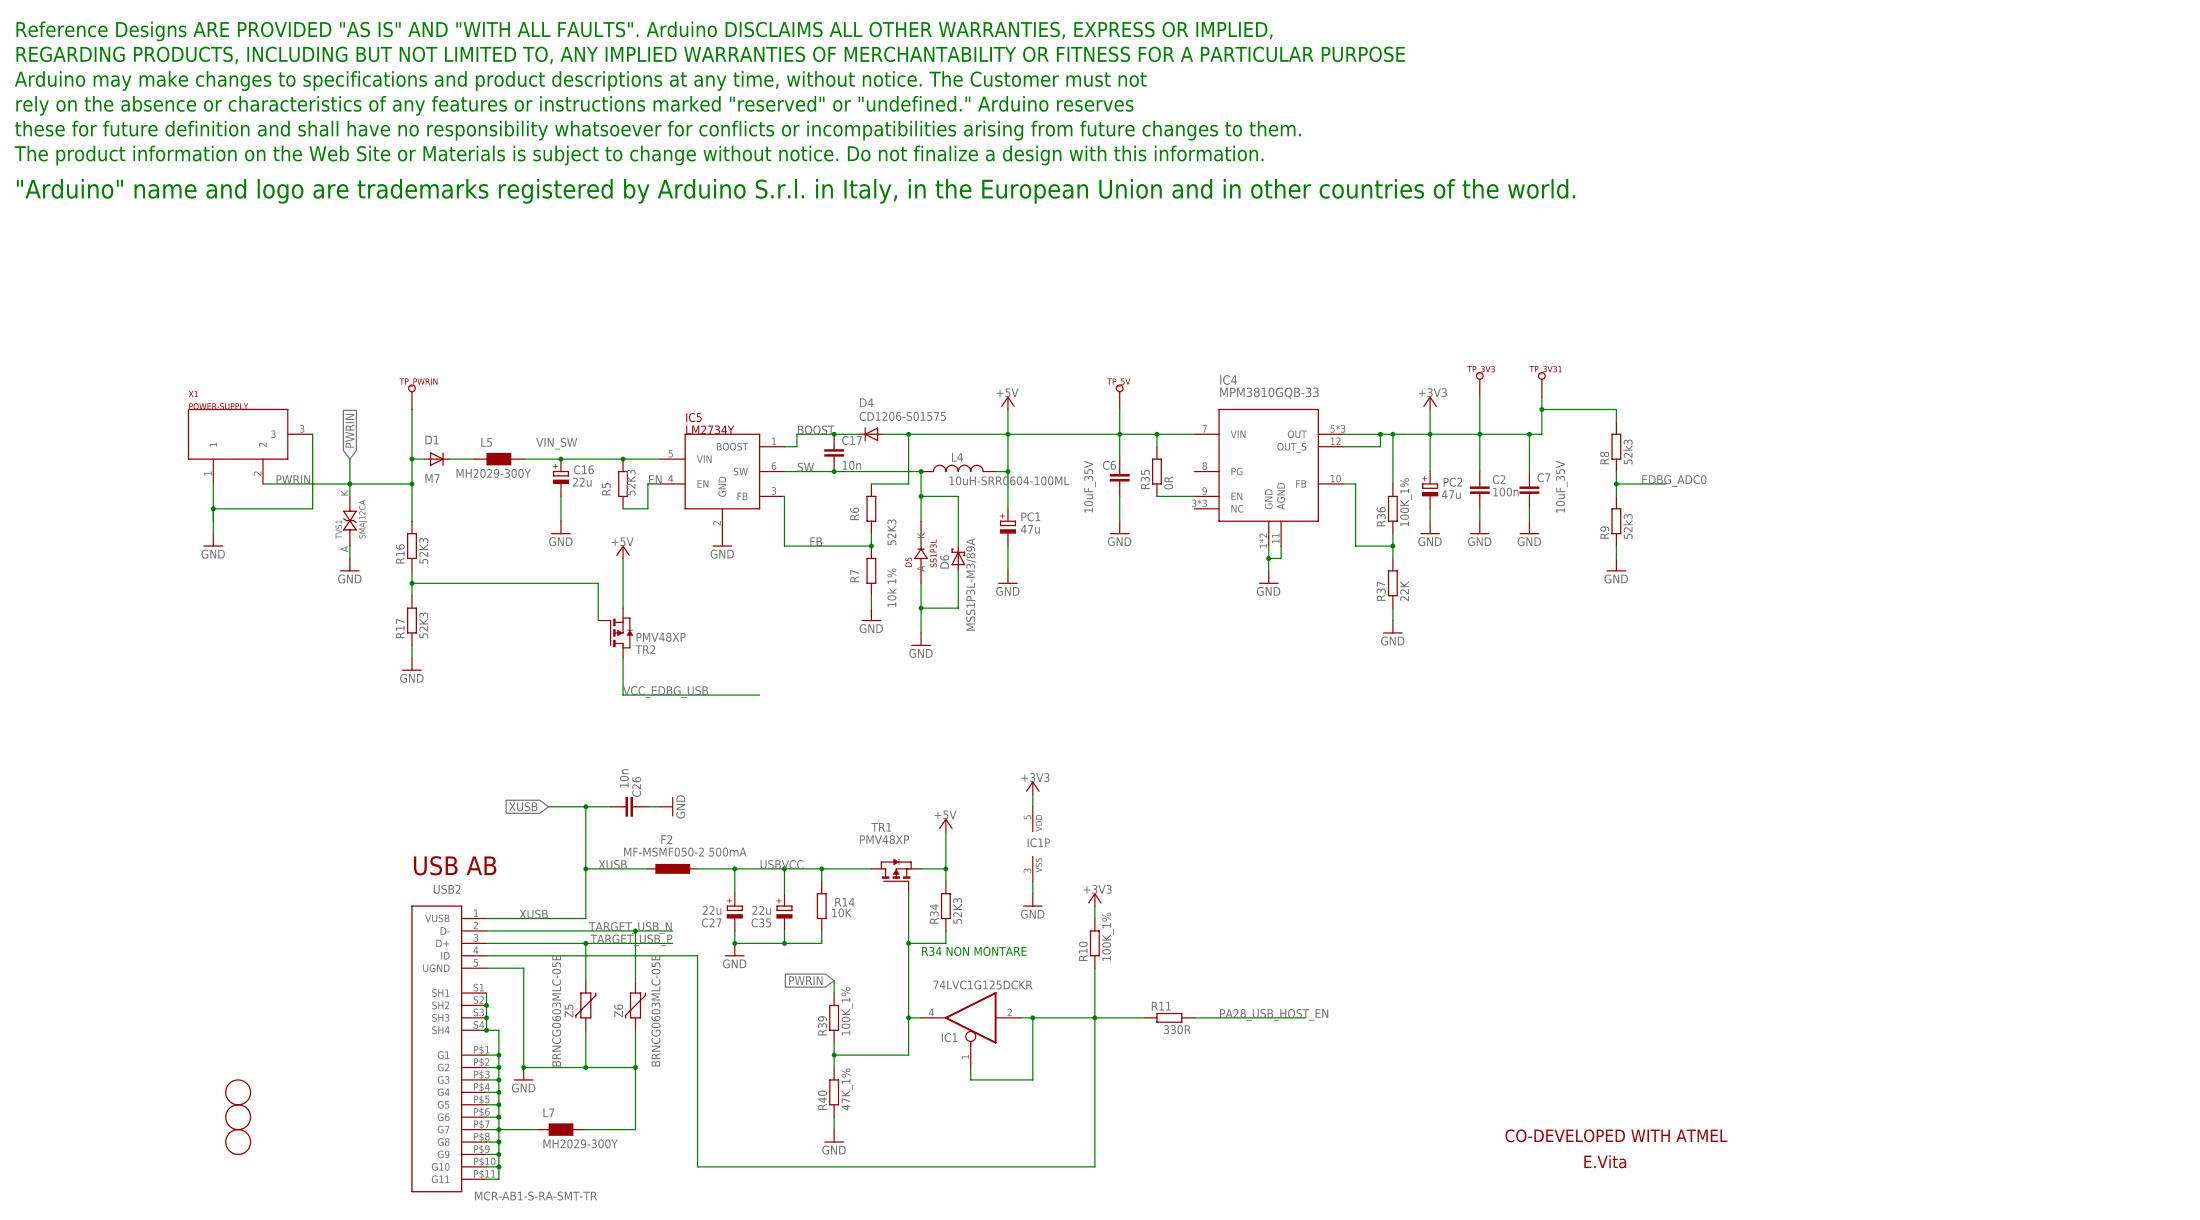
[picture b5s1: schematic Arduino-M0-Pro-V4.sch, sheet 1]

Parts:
C2: 100n; C0603-ROUND
C6, C7: 10uF_35V; C1210
C16, C27, C35: 22u; SMC_B
C17, C26: 10n; C0603-ROUND
D1: M7; SMB
D4: CD1206-S01575; MINIMELF
D5: SS1P3L; DO220AAL
D6: MSS1P3L-M3/89A; MICROSMP
F2: MF-MSMF050-2 500mA; L1812
FD1, FD2, FD3: FIDUCIALMOUNT; FIDUCIA-MOUNT
IC1: 74LVC1G125DCKR; SC70-5
IC4: MPM3810GQB-33; QFN-12
IC5: LM2734Y; SOT23-6
L4: 10uH-SRR0604-100ML; SRR0604
L5, L7: MH2029-300Y; 0805
PC1, PC2: 47u; PANASONIC_D
R5, R6, R16, R17, R34: 52K3; R0603-ROUND
R7: 10k 1%; R0603-ROUND
R8, R9: 52k3; R0603-ROUND
R10, R36, R39: 100K_1%; R0603-ROUND
R11: 330R; R0603-ROUND
R14: 10K; R0603-ROUND
R35: 0R; R0603-ROUND
R37: 22K; R0603-ROUND
R40: 47K_1%; R0603-ROUND
TP_3V3, TP_3V31, TP_5V: TP_SP; TP-SP
TP_PWRIN: TP_SP; TP-SP
TR1, TR2: PMV48XP; SOT-23
TVS1: SMAJ12CA; SMA-TVS
U$1: DISCLAIMER
USB2: MCR-AB1-S-RA-SMT-TR; MCR-AB1-S-RA-SMT
X1: POWER-SUPPLY; POWERSUPPLY_DC-21MM
Z5, Z6: BRNCG0603MLC-05E; CT/CN0603

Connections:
+3V3: C2.2, C7.1, IC1.5 (VDD), IC4.5 (OUT), IC4.6 (OUT), IC4.12 (OUT_S), IC4.14 (OUT), PC2.+, R8.2, R10.2, R36.2, TP_3V3.X, TP_3V31.X; also elsewhere on the board
+5V: C6.1, D4.A, IC4.7 (VIN), L4.P$2 (2), PC1.+, R6.1, R34.2, R35.2, TP_5V.X, TR1.2 (S), TR2.2 (S); also elsewhere on the board
BOOST: C17.1, D4.C, IC5.1 (BOOST)
EDBG_ADC0: R8.1, R9.2; also elsewhere on the board
EN: IC5.4 (EN), R5.2
FB: IC5.3 (FB), R6.2, R7.1
GND: C2.1, C6.2, C7.2, C16.-, C26.2, C27.-, C35.-, D5.P$2 (A), D6.A, IC1.3 (VSS), IC4.1 (GND), IC4.2 (GND), IC4.11 (AGND), IC5.2 (GND), L7.2, PC1.-, PC2.-, R7.2, R9.1, R14.1, R17.1, R37.1, R40.1, TVS1.A (AK), USB2.5 (UGND), X1.1, X1.3, Z5.2, Z6.2; also elsewhere on the board
unnamed: IC1.4 (O), R34.1, R39.1, R40.2, TR1.3 (G)
unnamed: IC1.1 (OE), IC1.2 (I), R10.1, R11.1, USB2.4 (ID)
unnamed: D1.C, L5.1
unnamed: IC4.9 (EN), R35.1
unnamed: IC4.10 (FB), R36.1, R37.2
unnamed: L7.1, USB2.P$1 (G1), USB2.P$2 (G2), USB2.P$3 (G3), USB2.P$4 (G4), USB2.P$5 (G5), USB2.P$6 (G6), USB2.P$7 (G7), USB2.P$8 (G8), USB2.P$9 (G9), USB2.P$10 (G10), USB2.P$11 (G11), USB2.S1 (SH1), USB2.S2 (SH2), USB2.S3 (SH3), USB2.S4 (SH4)
unnamed: R16.1, R17.2, TR2.3 (G)
PA28_USB_HOST_EN: R11.2; also elsewhere on the board
PWRIN: D1.A, R16.2, R39.2, TP_PWRIN.X, TVS1.K (KA), X1.2; also elsewhere on the board
SW: C17.2, D5.P$1 (K), D6.K (C), IC5.6 (SW), L4.P$1 (1)
TARGET_USB_N: USB2.2 (D-), Z6.1; also elsewhere on the board
TARGET_USB_P: USB2.3 (D+), Z5.1; also elsewhere on the board
USBVCC: C27.+, C35.+, F2.1, R14.2, TR1.1 (D)
VCC_EDBG_USB: TR2.1 (D); also elsewhere on the board
VIN_SW: C16.+, IC5.5 (VIN), L5.2, R5.1
XUSB: C26.1, F2.2, USB2.1 (VUSB)

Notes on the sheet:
USB AB
E.Vita
CO-DEVELOPED WITH ATMEL
R34 NON MONTARE
